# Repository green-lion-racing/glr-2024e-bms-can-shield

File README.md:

# CAN-Shield for NUCLEO-G474RE

NUCLEO-G474RE compatible CAN shield, which is our main microcontroller for the battery management system (BMS/AMS).

### Overview

Acts as can transciever for the BMS. 
Has two 12V output pins, one in case of a BMS fault. The other to set the state (on/off) of the HV charger.

CAN 1 is designated for the communication with FSGs datalogger, because of the high 1Mbit CAN baudrate.

CAN 2 is designated to communicate with the rest of the car, at a lower baudrate.

Compatible to the Analog Devices EVAL-ADBMS6822 board, can be directly slotted onto the nucleo board at the same time.

WR-TBL 3.5mm Connectors for signals to and from the board.

### Used parts

> [!WARNING]  
> Part list is not complete.

| Article                          | Description                  | Link                                                                                                                                        | Quantity |
| -------------------------------- | ---------------------------- | ------------------------------------------------------------------------------------------------------------------------------------------- | -------- |
| Infineon TLE6250GV33XUMA1        | can transiever               | https://www.mouser.de/ProductDetail/Infineon-Technologies/TLE6250GV33XUMA1?qs=OwbwYO03UsJ9UcCPEQ3lNA%3D%3D                                  | 2        |
| Omron G5V-2-DC12                 | relais                       | https://www.mouser.de/ProductDetail/Omron-Electronics/G5V-2-DC12?qs=lK7M36XCk6JxdWY%2FV6sVqw%3D%3D                                          | 1        |
| STMicroelectronics ESDCAN01-2BLY | dual-line TVS diode          | https://www.mouser.de/ProductDetail/STMicroelectronics/ESDCAN01-2BLY?qs=Ok1pvOkw6%2FpNzC2RQnWwPA%3D%3D                                      | 2        |
|                                  | transistor                   |                                                                                                                                             |          |
| Samsung CL10B104KB8NNNC          | capacitor 100nF              | https://www.mouser.de/ProductDetail/Samsung-Electro-Mechanics/CL10B104KB8NNNC?qs=349EhDEZ59rvGc2rLwVOdA%3D%3D                               | 2        |
| Vishay CRCW060368R1FKEA          | resistor 68ohm               | https://www.mouser.de/ProductDetail/Vishay-Dale/CRCW060368R1FKEA?qs=6z8JnUK2jyMngsBXu5il1A%3D%3D                                            | 4        |
| Samtec SSW-119-01-T-D-LL         | 02x19  Mounting Pin, 2.54 mm | https://www.mouser.de/ProductDetail/Samtec/SSW-119-01-T-D-LL?qs=F1JzWfReSMQC5N%252BZEM9ULw%3D%3D                                            | 2        |
| Würth Elektronik 691321100002    | 2-pin header                 | https://www.mouser.de/ProductDetail/Wurth-Elektronik/691321100002?qs=sGAEpiMZZMvPvGwLNS6715pX%252BQgp6lhzMFLUiDaj9KJjOeguQ8XvHQ%3D%3D       | 1        |
| Würth Elektronik 691361100002    | 2-pin plug                   | https://www.mouser.de/ProductDetail/Wurth-Elektronik/691361100002?qs=sGAEpiMZZMvPvGwLNS6715pX%252BQgp6lhzc8iD6dL%252BnREnLxTu%2F6qxUQ%3D%3D | 1        |
| Würth Elektronik 691321100004    | 4-pin header                 | https://www.mouser.de/ProductDetail/Wurth-Elektronik/691321100004?qs=sGAEpiMZZMvPvGwLNS6716dt6ZVWwiEWhH92dgOeUJ3PgxyzktJ1Fw%3D%3D           | 2        |
| Würth Elektronik 691361100004    | 4-pin plug                   | https://www.mouser.de/ProductDetail/Wurth-Elektronik/691361100004?qs=2kOmHSv6VfRmrzXJBP%2F4Sg%3D%3D                                         | 2        |

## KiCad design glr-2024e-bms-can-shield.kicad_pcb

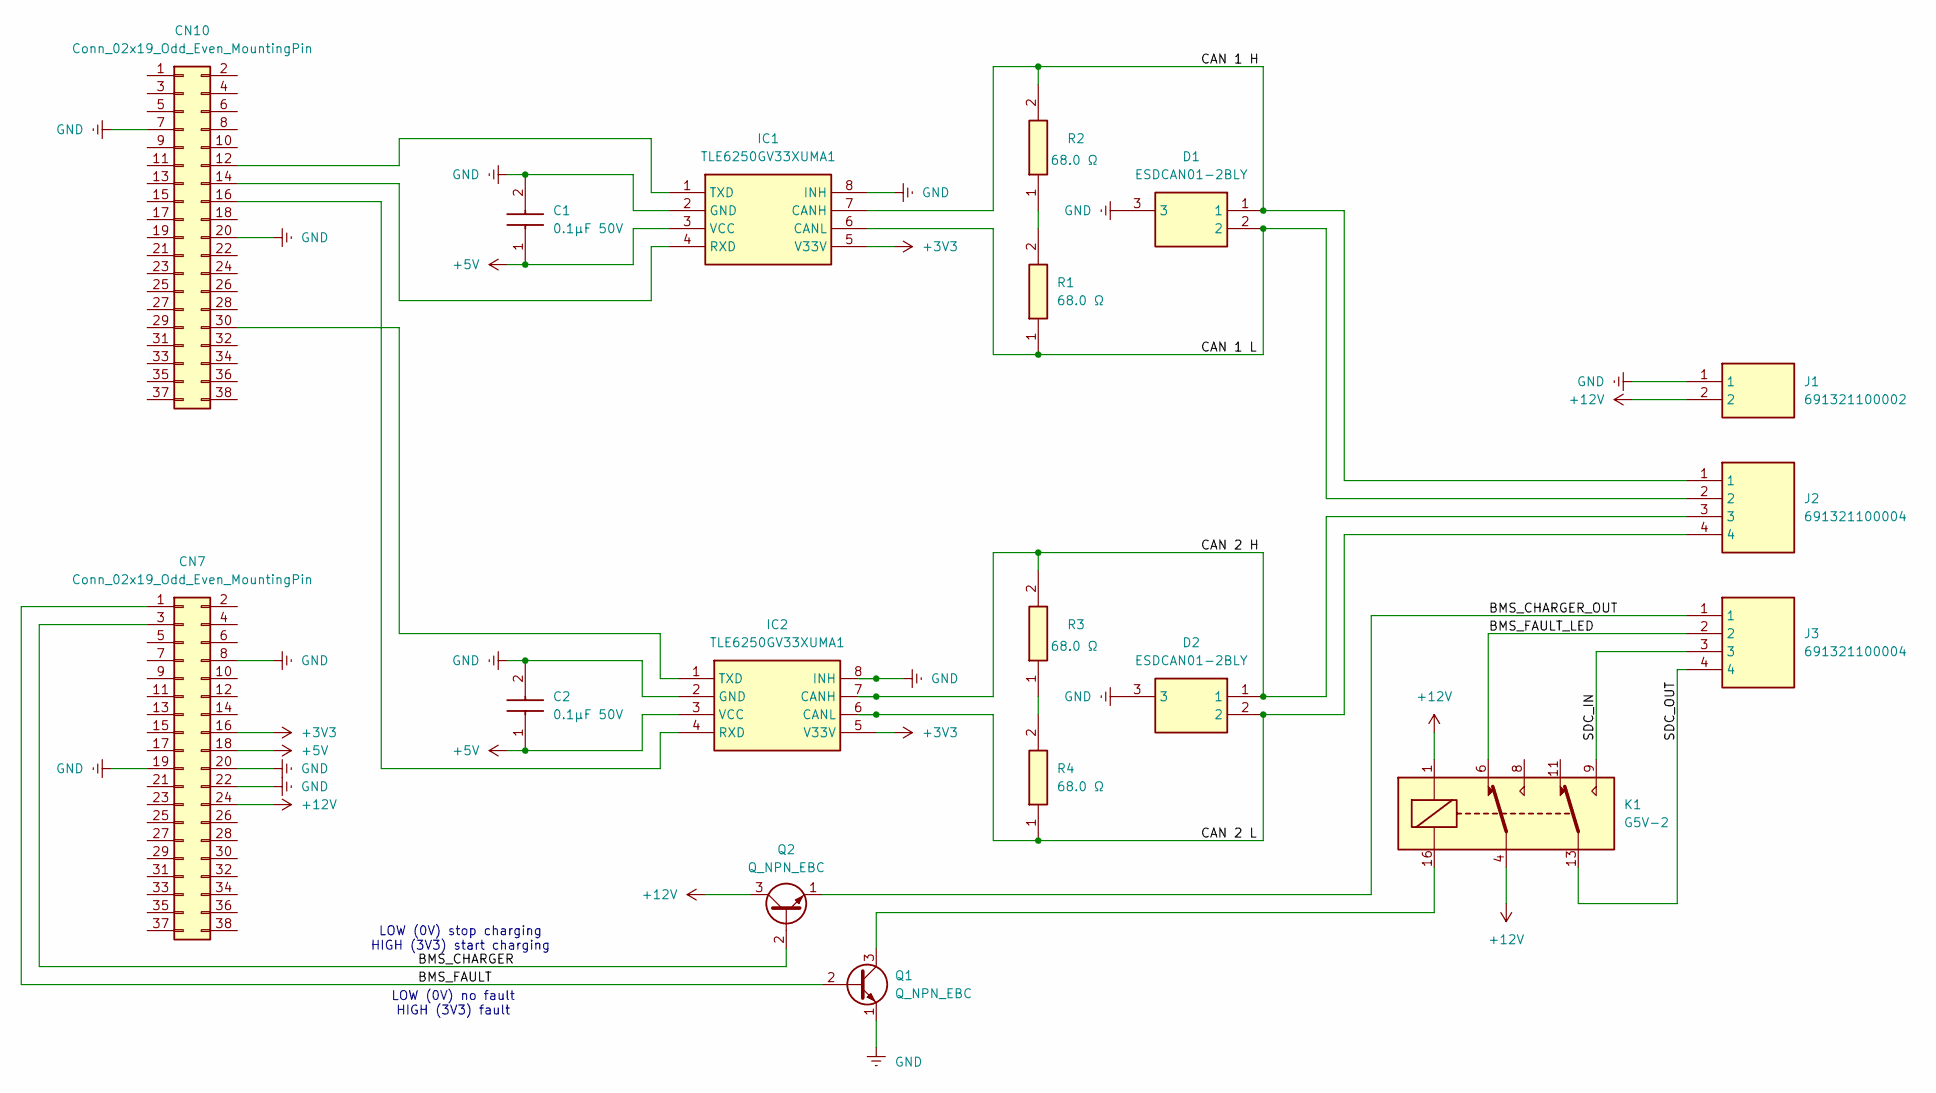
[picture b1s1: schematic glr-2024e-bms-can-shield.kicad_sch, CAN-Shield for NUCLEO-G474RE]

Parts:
C1, C2: 0.1μF 50V; CAPC1608X90N; Manufacturer_Part_Number CL10B104KB8NNNC
CN7, CN10: Conn_02x19_Odd_Even_MountingPin; PinSocket_2x19_P2.54mm_Vertical
D1, D2: ESDCAN01-2BLY; SOT95P255X125-3N; Mouser Part Number 511-ESDCAN01-2BLY
IC1, IC2: TLE6250GV33XUMA1; SOIC127P600X175-8N; Mouser Part Number 726-TLE6250GV33XUMA1
J1: 691321100002; Mouser Part Number 710-691321100002
J2, J3: 691321100004; Mouser Part Number 710-691321100004
K1: G5V-2; Relay_DPDT_Omron_G5V-2
Q1: Q_NPN_EBC; TO-18-3
Q2: Q_NPN_EBC; SOT-23
R1, R2, R3, R4: 68.0 Ω; RESC1608X50N; Manufacturer_Part_Number CRCW060368R1FKEA

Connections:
+3V3: CN7.16, IC1.5 (V33V), IC2.5 (V33V)
+5V: C1.1, C2.1, CN7.18, IC1.3 (VCC), IC2.3 (VCC)
+12V: CN7.24, J1.2, K1.1, K1.4, Q2.3 (C)
/BMS_CHARGER: CN7.3, Q2.2 (B)
/BMS_CHARGER_OUT: J3.1, Q2.1 (E)
/BMS_FAULT: CN7.1, Q1.2 (B)
/BMS_FAULT_LED: J3.2, K1.6
/CAN 1 H: D1.1, IC1.7 (CANH), J2.1, R2.2
/CAN 1 L: D1.2, IC1.6 (CANL), J2.2, R1.1
/CAN 2 H: D2.1, IC2.7 (CANH), J2.3, R3.2
/CAN 2 L: D2.2, IC2.6 (CANL), J2.4, R4.1
/SDC_IN: J3.3, K1.9
/SDC_OUT: J3.4, K1.13
GND: C1.2, C2.2, CN7.8, CN7.19, CN7.20, CN7.22, CN10.7, CN10.20, D1.3, D2.3, IC1.2 (GND), IC1.8 (INH), IC2.2 (GND), IC2.8 (INH), J1.1, Q1.1 (E)
unnamed: CN10.12, IC1.1 (TXD)
unnamed: CN10.14, IC1.4 (RXD)
unnamed: CN10.16, IC2.4 (RXD)
unnamed: CN10.30, IC2.1 (TXD)
unnamed: K1.16, Q1.3 (C)
unnamed: R1.2, R2.1
unnamed: R3.1, R4.2

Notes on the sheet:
LOW (0V) stop charging HIGH (3V3) start charging
LOW (0V) no fault HIGH (3V3) fault

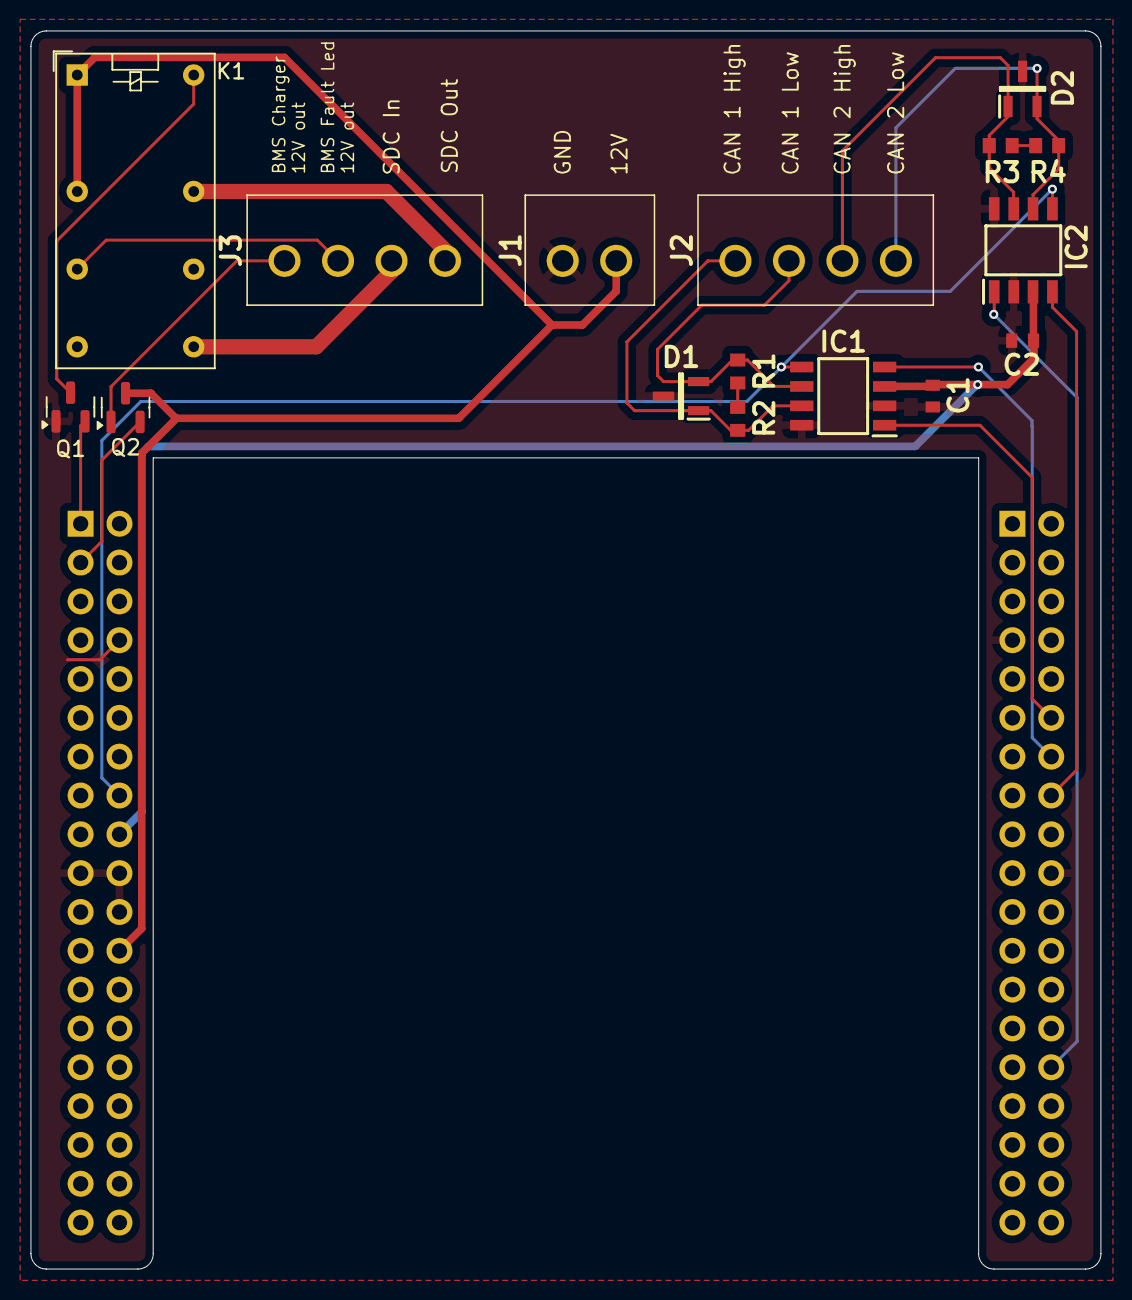
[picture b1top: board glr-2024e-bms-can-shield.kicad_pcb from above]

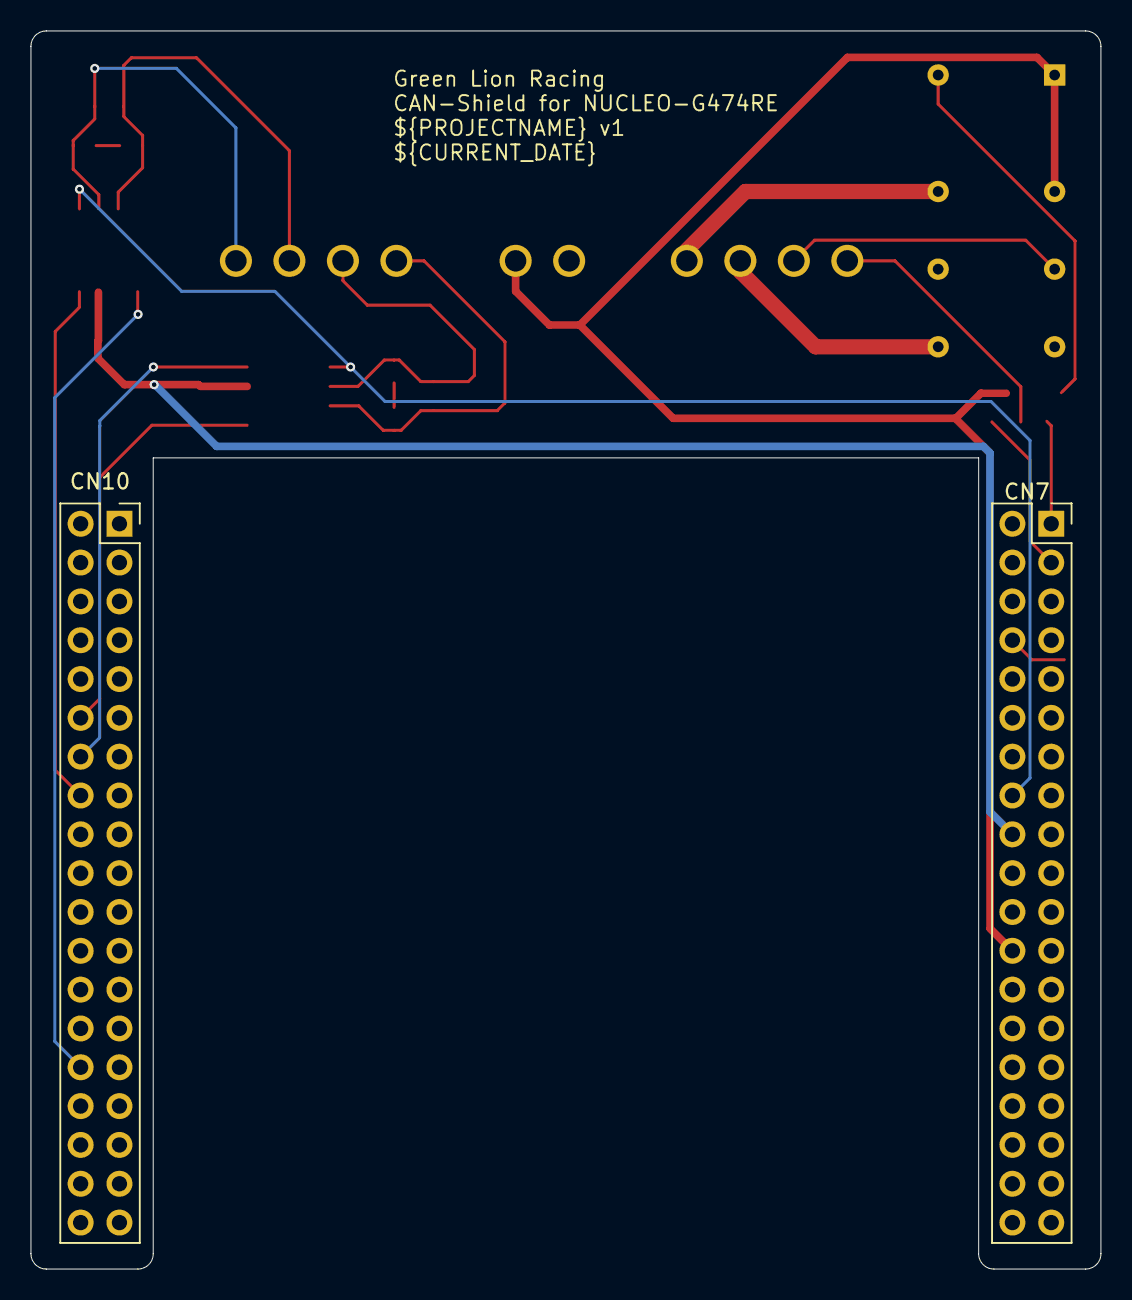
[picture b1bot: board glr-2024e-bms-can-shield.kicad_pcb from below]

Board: 2 copper layers, 70.0 x 81.0 mm, 18 parts (2 on the bottom side), 21 nets.

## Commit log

2025-06-07 Initial commit
    pcb should be done
2025-06-11 remove temp file
2025-06-13 Update LICENSE
2025-06-19 add relay and optocopler
2025-06-21 the last touch
    I added two transistors. The first one replaces the optocoupler and controls the relay: when 3.3 V is present at the input (which indicates a fault), the transistor switches on and activates the rela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
    The second transistor is used to turn the charger on and off. For this purpose, it was necessary to connect 12 V to its collector.
2025-06-21 more details to understand
    explaining how work the process between the socket and the transistors
2025-06-22 use Würth Elektronik TBL connectors
    do some restructuring
    add project specific libraries
2025-06-23 .gitignore not working?
2025-06-23 set output path
2025-06-24 nvm the .gitignore does work
    there were files inside root directory lol
2025-06-24 update needed parts
    not sure about these transistors
    add pdf to ignore list
2025-06-24 forgor to save the file
    add plot output directory
2025-06-25 use current date as variable
